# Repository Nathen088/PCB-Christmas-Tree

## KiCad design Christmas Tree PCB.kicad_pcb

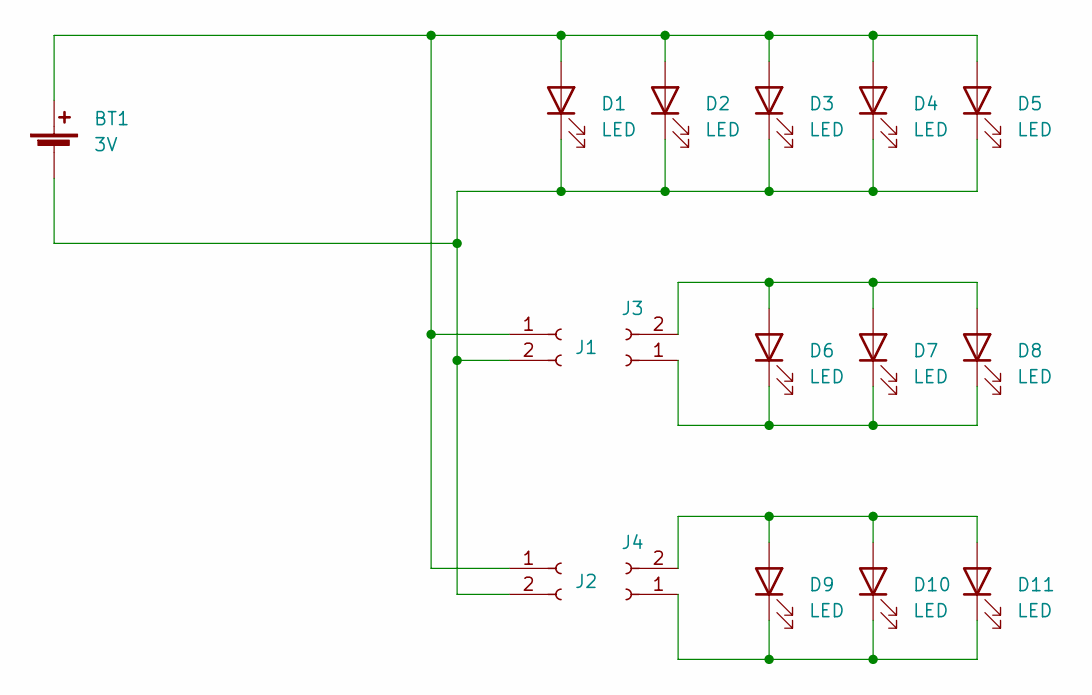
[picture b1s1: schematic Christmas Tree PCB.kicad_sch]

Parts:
BT1: 3V; BatteryHolder_Keystone_3002_1x2032
D1, D2, D3, D4, D5, D6, D7, D8, D9, D10, D11: LED; LED_D5.0mm
J1, J2, J3, J4: Conn_01x02_Female; PinSocket_1x02_P2.54mm_Vertical

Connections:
unnamed: BT1.1 (+), D1.2 (A), D2.2 (A), D3.2 (A), D4.2 (A), D5.2 (A), J1.1, J2.1
unnamed: BT1.2 (-), D1.1 (K), D2.1 (K), D3.1 (K), D4.1 (K), D5.1 (K), J1.2, J2.2
unnamed: D6.1 (K), D7.1 (K), D8.1 (K), J3.1
unnamed: D6.2 (A), D7.2 (A), D8.2 (A), J3.2
unnamed: D9.1 (K), D10.1 (K), D11.1 (K), J4.1
unnamed: D9.2 (A), D10.2 (A), D11.2 (A), J4.2

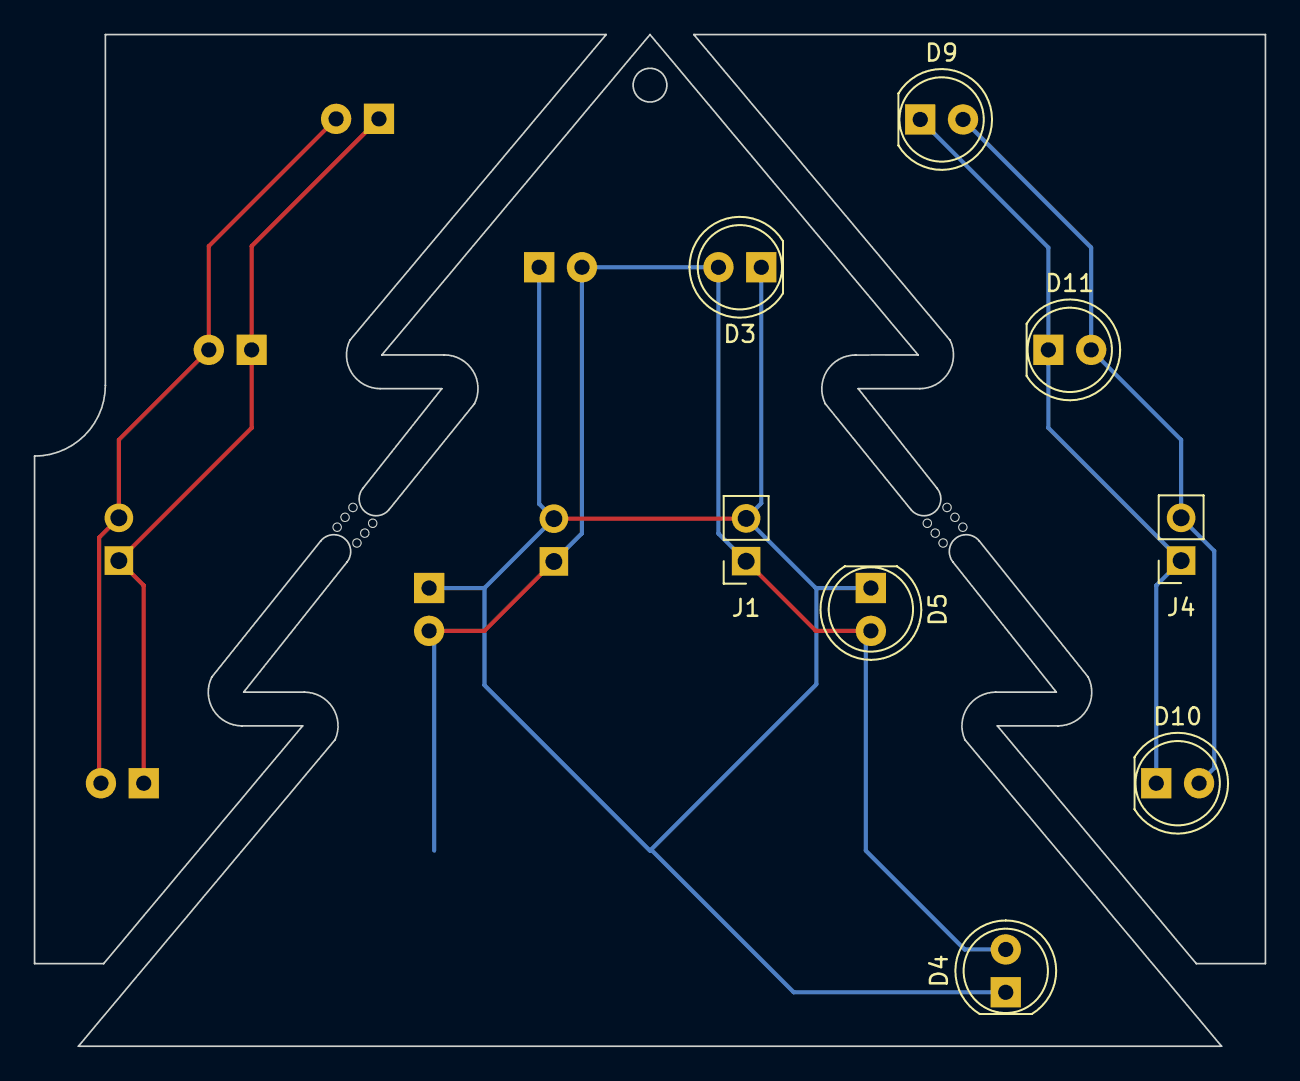
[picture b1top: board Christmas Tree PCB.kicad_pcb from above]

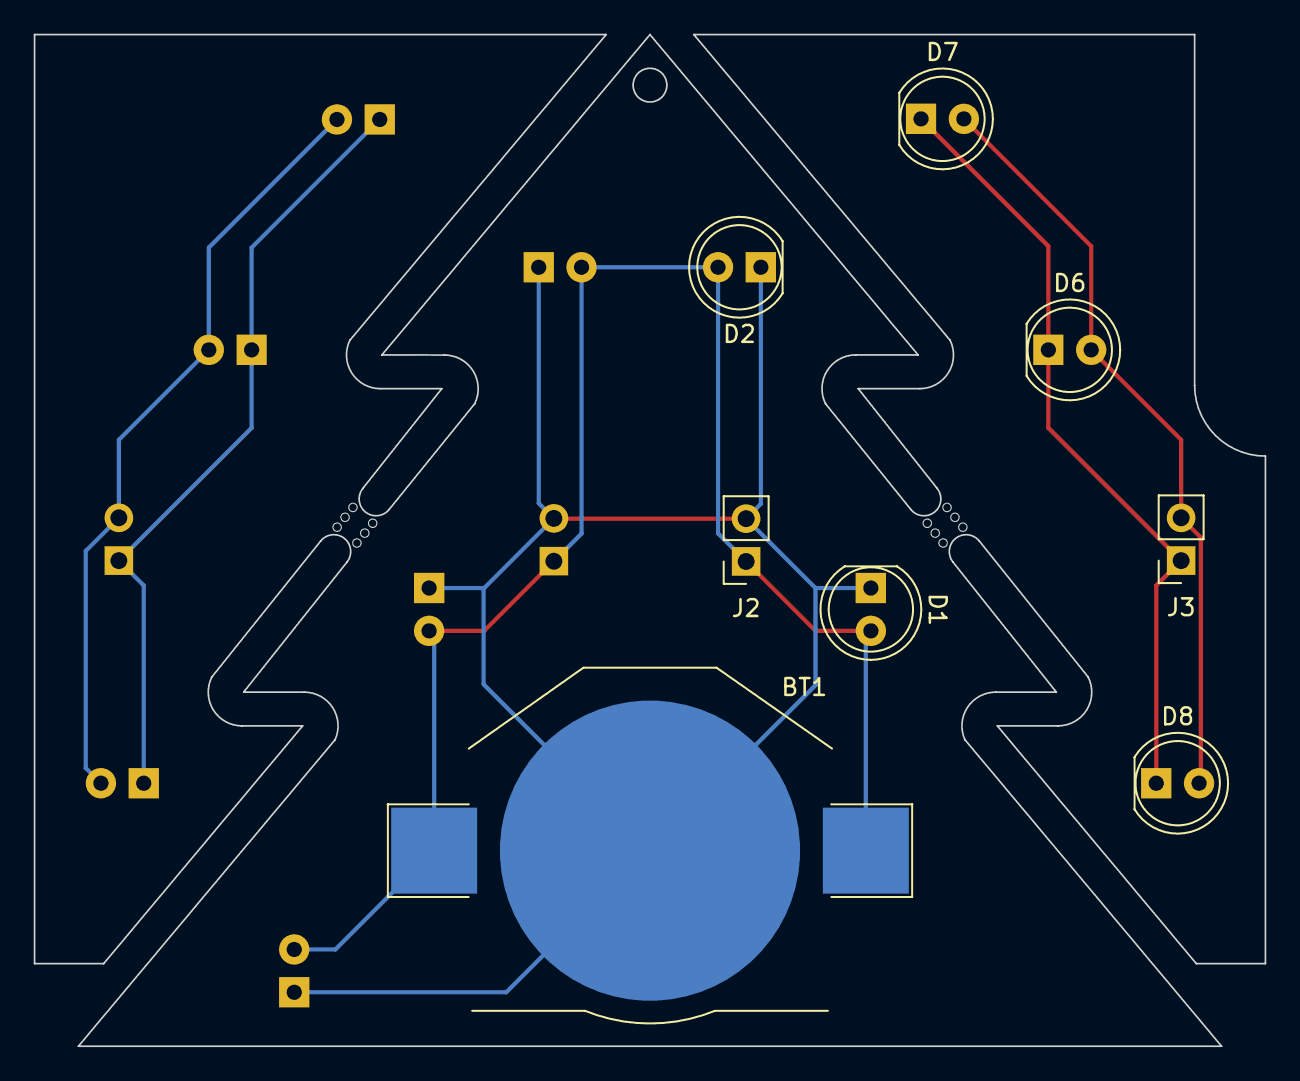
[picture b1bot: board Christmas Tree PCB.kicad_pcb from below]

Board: 2 copper layers, 73.0 x 60.0 mm, 18 parts (9 on the bottom side), 6 nets.

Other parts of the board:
mouse-bite-2mm-slot, mouse-bite-2mm-slot#2: VAL**; mouse-bite-2mm-slot
